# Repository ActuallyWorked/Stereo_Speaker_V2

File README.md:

# Stereo_Speaker_V2
ECE5 extra credit assignment tasked students with designing a PCB from a provided mono-amplifier schematic. This is an extended version with the following modifications:

Converted the mono circuit into stereo, added a band-pass filter (80Hz-16kHz), 9V regulator, LED power indicator, and integrated with a 100W USB-C PD module from Aliexpress to allow for 100W charging/discharging for mobile devices if needed.

Reasoning: 

Band-pass filter was used to compensate for the extra-long audio cable

9V regulator was used to allow for other power sources besides the in-class 9V alkaline battery -- allowed for Li-ion battery pack to be used and for the use of the 100W USB-C module)

LED power indicator was used to reduce power loss on the LDO and was a nice-to-have feature

100W USB-C module was added because I wanted a battery bank, and I realized I could make a speaker and portable battery at the same time.

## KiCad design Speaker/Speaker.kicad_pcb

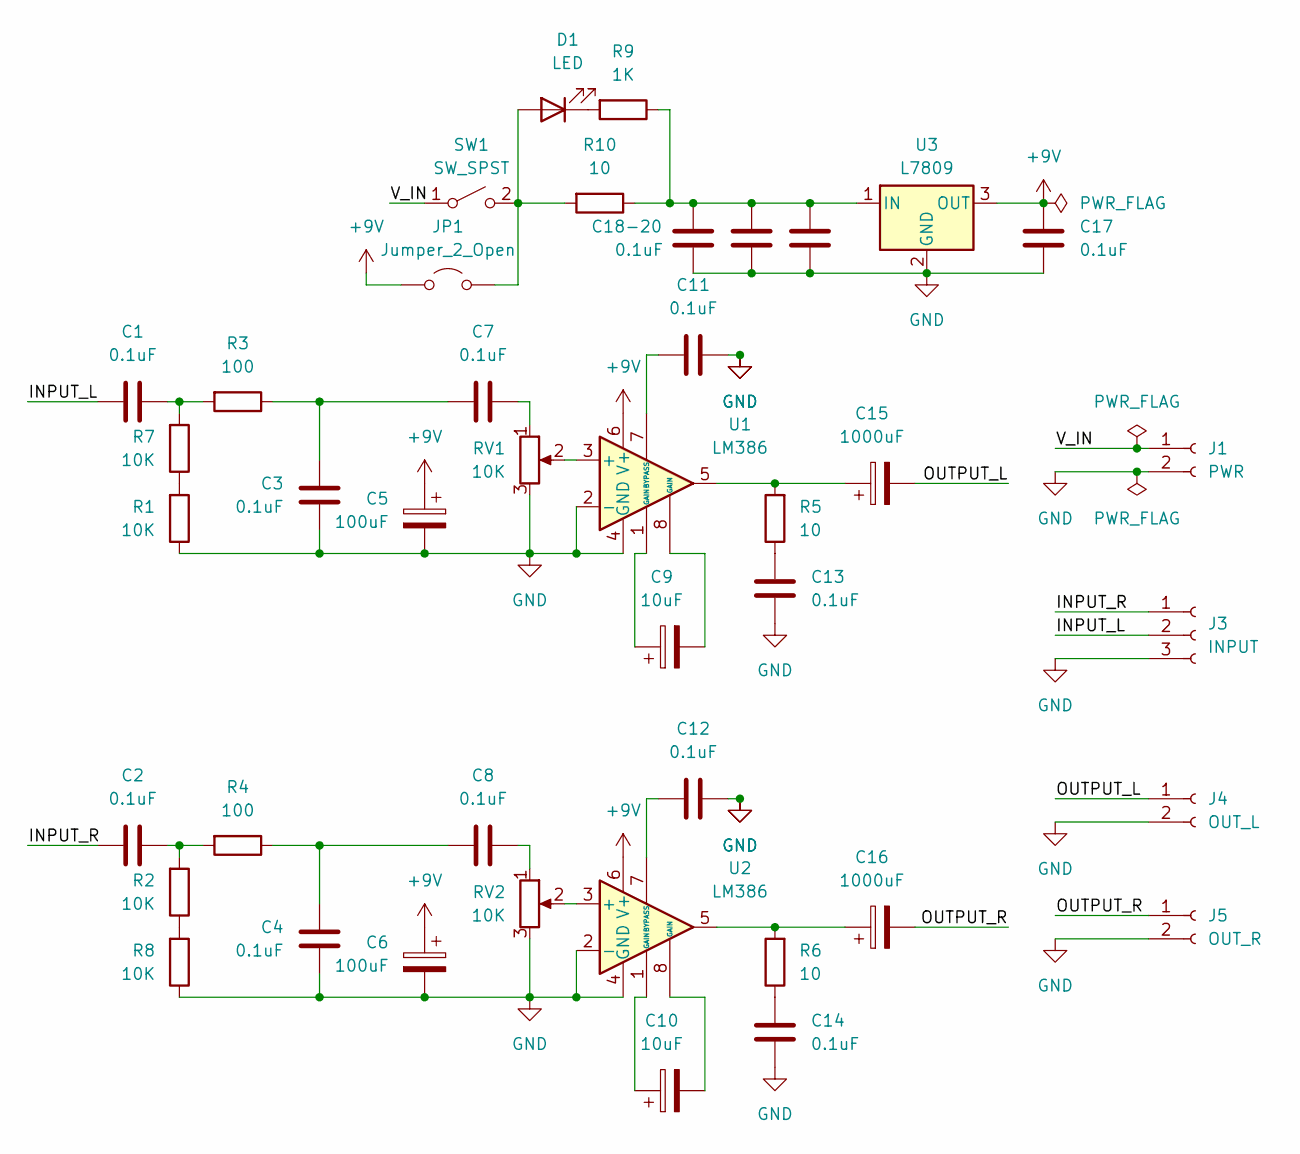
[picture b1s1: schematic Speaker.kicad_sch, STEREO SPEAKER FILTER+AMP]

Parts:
C1, C2, C3, C4, C7, C8, C11, C12, C13, C14, C17, C18-20, C19, C20: 0.1uF; C_Disc_D3.0mm_W1.6mm_P2.50mm
C5, C6: 100uF; CP_Radial_D8.0mm_P2.50mm
C9, C10: 10uF; CP_Radial_D10.0mm_P5.00mm
C15, C16: 1000uF; CP_Radial_D10.0mm_P5.00mm
D1: LED; LED_D5.0mm
J1: PWR; PinSocket_1x02_P2.54mm_Vertical
J3: INPUT; PinSocket_1x03_P2.54mm_Vertical
J4: OUT_L; PinSocket_1x02_P2.54mm_Vertical
J5: OUT_R; PinSocket_1x02_P2.54mm_Vertical
JP1: Jumper_2_Open; SolderJumper-2_P1.3mm_Open_TrianglePad1.0x1.5mm
R1, R2, R7, R8: 10K; R_Axial_DIN0207_L6.3mm_D2.5mm_P10.16mm_Horizontal
R3, R4: 100; R_Axial_DIN0207_L6.3mm_D2.5mm_P10.16mm_Horizontal
R5, R6, R10: 10; R_Axial_DIN0207_L6.3mm_D2.5mm_P10.16mm_Horizontal
R9: 1K; R_Axial_DIN0207_L6.3mm_D2.5mm_P10.16mm_Horizontal
RV1, RV2: 10K; Potentiometer_Bourns_3386C_Horizontal
SW1: SW_SPST; PinSocket_1x02_P2.54mm_Vertical
U1, U2: LM386; DIP-8_W7.62mm
U3: L7809; TO-220-3_Vertical

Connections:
+9V: C5.1, C6.1, C17.1, JP1.1 (A), U1.6 (V+), U2.6 (V+), U3.3 (OUT); also elsewhere on the board
/INPUT_L: C1.2, J3.2
/INPUT_R: C2.2, J3.1
/OUTPUT_L: C15.2, J4.1
/OUTPUT_R: C16.2, J5.1
/V_IN: J1.1, SW1.1 (A)
GND: C3.2, C4.2, C5.2, C6.2, C11.2, C12.2, C13.1, C14.1, C17.2, C18-20.2, C19.2, C20.2, J1.2, J3.3, J4.2, J5.2, R1.1, R8.1, RV1.3, RV2.3, U1.2 (-), U1.4 (GND), U2.2 (-), U2.4 (GND), U3.2 (GND); also elsewhere on the board
unnamed: C1.1, R3.2, R7.2
unnamed: C2.1, R2.2, R4.2
unnamed: C3.1, C7.2, R3.1
unnamed: C4.1, C8.2, R4.1
unnamed: C7.1, RV1.1
unnamed: C8.1, RV2.1
unnamed: C9.1, U1.1 (GAIN)
unnamed: C9.2, U1.8 (GAIN)
unnamed: C10.1, U2.1 (GAIN)
unnamed: C10.2, U2.8 (GAIN)
unnamed: C13.2, R5.1
unnamed: C14.2, R6.1
unnamed: C15.1, R5.2, U1.5
unnamed: C16.1, R6.2, U2.5
unnamed 21: D1.2 (A), JP1.2 (B), R10.2, SW1.2 (B); also elsewhere on the board
unnamed: D1.1 (K), R9.2
unnamed: R1.2, R7.1
unnamed: R2.1, R8.2
unnamed: RV1.2, U1.3 (+)
unnamed: C11.1, U1.7 (BYPASS)
unnamed: RV2.2, U2.3 (+)
unnamed: C12.1, U2.7 (BYPASS)
unnamed 29: C18-20.1, C19.1, C20.1, R9.1, R10.1, U3.1 (IN); also elsewhere on the board

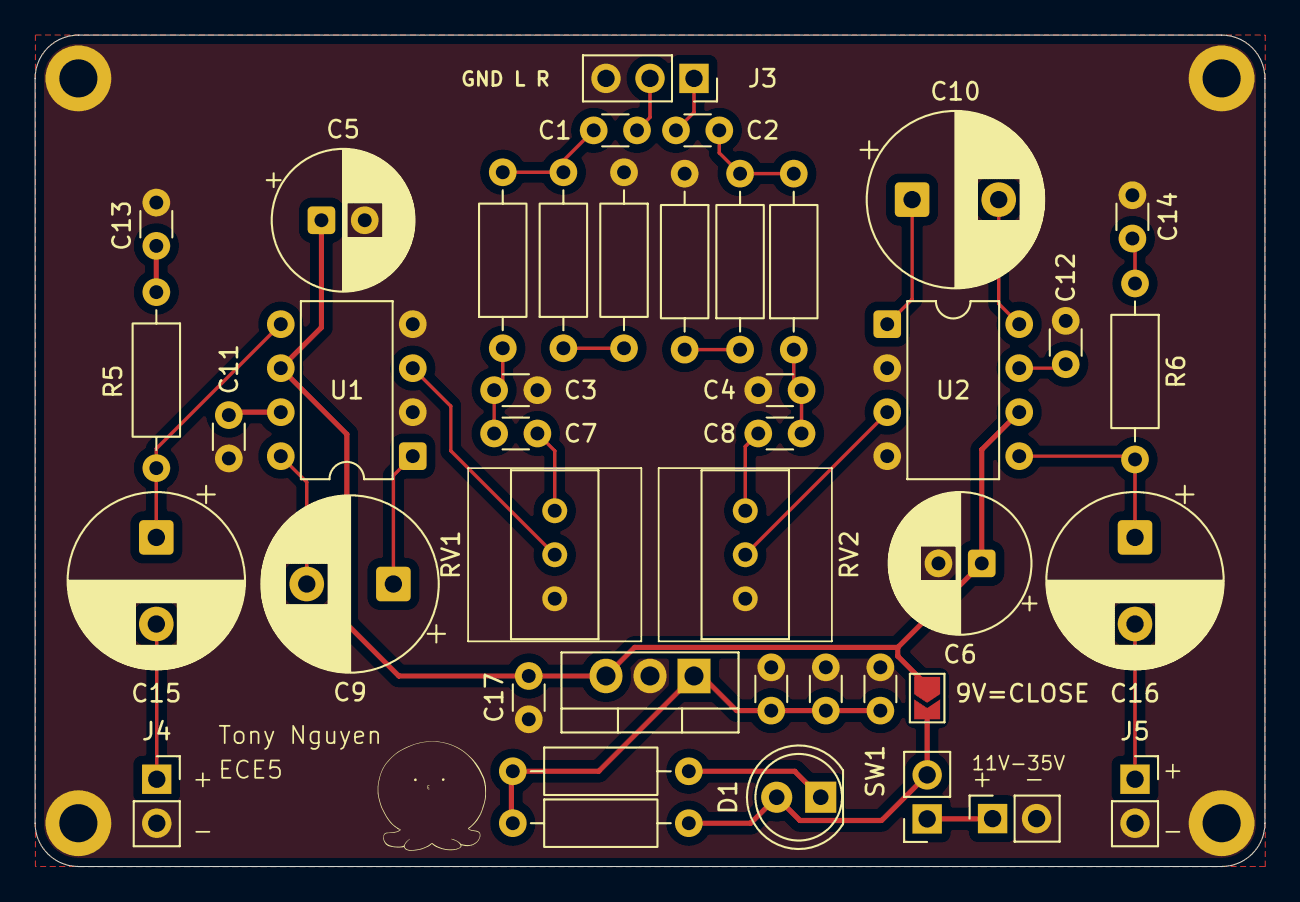
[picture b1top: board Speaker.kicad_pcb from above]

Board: 2 copper layers, 71.0 x 48.0 mm, 42 parts (0 on the bottom side), 30 nets.

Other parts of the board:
9V=CLOSE: Jumper_2_Open; SolderJumper-2_P1.3mm_Open_TrianglePad1.0x1.5mm
C18: 0.1uF; C_Disc_D3.0mm_W1.6mm_P2.50mm

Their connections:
+9V: 9V=CLOSE.1 (A); also elsewhere on the board
GND: C18.2; also elsewhere on the board
unnamed 21: 9V=CLOSE.2 (B); also elsewhere on the board
unnamed 29: C18.1; also elsewhere on the board
